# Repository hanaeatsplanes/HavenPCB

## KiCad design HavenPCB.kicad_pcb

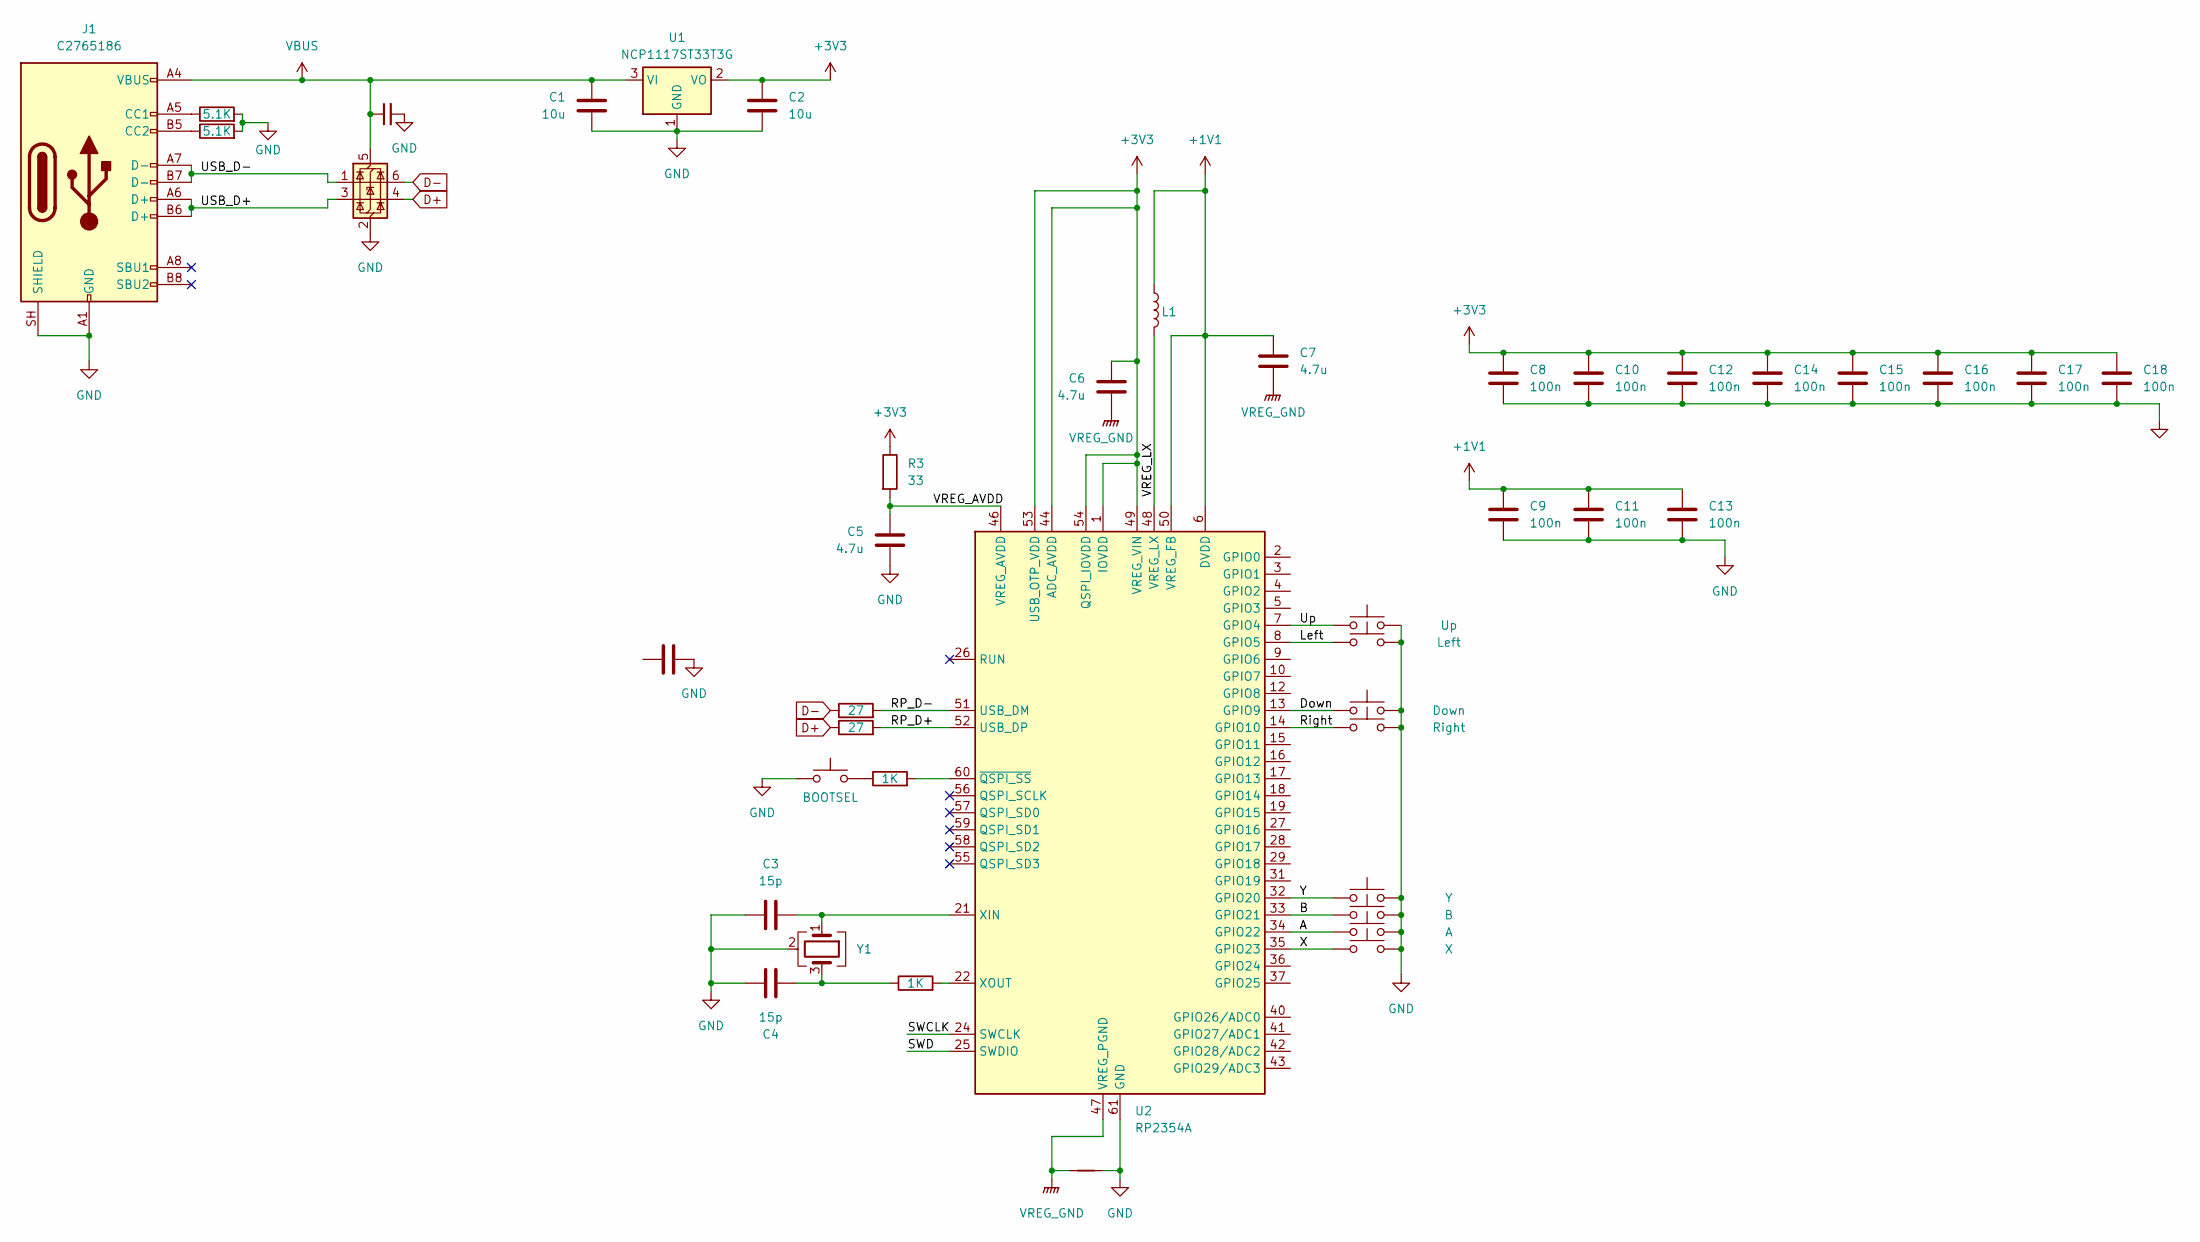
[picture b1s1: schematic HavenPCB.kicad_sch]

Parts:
C1, C2: 10u; C_0402_1005Metric
C3, C4: 15p; C_0402_1005Metric
C5, C6, C7, C22: 4.7u; C_0402_1005Metric
C8, C9, C10, C11, C12, C13, C14, C15, C16, C17, C18, C19: 100n; C_0402_1005Metric
J1: C2765186; USB-C-SMD_TYPE-C-16PIN-2MD-073
L1: AOTA-B201610S3R3-101-T; L_0805_2012Metric
NT1: NetTie_2; NetTie-2_SMD_Pad2.0mm
R1, R2: 5.1K; R_0402_1005Metric
R3: 33; R_0402_1005Metric
R4, R5: 1K; R_0402_1005Metric
R6, R7: 27; R_0603_1608Metric
SW1: BOOTSEL; SW_SPST_TS-1088-xR020
SW2: Up; SW_PUSH_6mm_H5mm
SW3: Right; SW_PUSH_6mm_H5mm
SW4: Left; SW_PUSH_6mm_H5mm
SW5: Down; SW_PUSH_6mm_H5mm
SW6: X; SW_PUSH_6mm_H5mm
SW7: Y; SW_PUSH_6mm_H5mm
SW8: B; SW_PUSH_6mm_H5mm
SW9: A; SW_PUSH_6mm_H5mm
U1: NCP1117ST33T3G; SOT-223-3_TabPin2
U2: RP2354A; QFN-60-1EP_7x7mm_P0.4mm_EP3.4x3.4mm
U3: USBLC6-2SC6; SOT-23-6
Y1: ABM8-272-T3; Crystal_SMD_3225-4Pin_3.2x2.5mm

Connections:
+1V1: C7.1, C9.1, C11.1, C13.1, L1.2, U2.6 (DVDD), U2.23 (DVDD), U2.39 (DVDD), U2.50 (VREG_FB)
+3V3: C2.1, C6.1, C8.1, C10.1, C12.1, C14.1, C15.1, C16.1, C17.1, C18.1, R3.1, U1.2 (VO), U2.1 (IOVDD), U2.11 (IOVDD), U2.20 (IOVDD), U2.30 (IOVDD), U2.38 (IOVDD), U2.44 (ADC_AVDD), U2.45 (IOVDD), U2.49 (VREG_VIN), U2.53 (USB_OTP_VDD), U2.54 (QSPI_IOVDD)
/A: SW9.1, U2.34 (GPIO22)
/B: SW8.1, U2.33 (GPIO21)
/Down: SW5.1, U2.13 (GPIO9)
/Left: SW4.1, U2.8 (GPIO5)
/RP_D+: R7.2, U2.52 (USB_DP)
/RP_D-: R6.2, U2.51 (USB_DM)
/Right: SW3.1, U2.14 (GPIO10)
/SWCLK: U2.24 (SWCLK)
/SWD: U2.25 (SWDIO)
/USB_D+: J1.A6 (D+), J1.B6 (D+), U3.3 (I/O2)
/USB_D-: J1.A7 (D-), J1.B7 (D-), U3.1 (I/O1)
/Up: SW2.1, U2.7 (GPIO4)
/VREG_AVDD: C5.1, R3.2, U2.46 (VREG_AVDD)
/VREG_LX: L1.1, U2.48 (VREG_LX)
/X: SW6.1, U2.35 (GPIO23)
/Y: SW7.1, U2.32 (GPIO20)
D+: R7.1, U3.4 (I/O2)
D-: R6.1, U3.6 (I/O1)
GND: C1.2, C2.2, C3.1, C4.1, C5.2, C8.2, C9.2, C10.2, C11.2, C12.2, C13.2, C14.2, C15.2, C16.2, C17.2, C18.2, C19.2, C22.2, J1.A1 (GND), J1.A12 (GND), J1.B1 (GND), J1.B12 (GND), J1.SH (SHIELD), NT1.2, R1.2, R2.2, SW1.1, SW2.2, SW3.2, SW4.2, SW5.2, SW6.2, SW7.2, SW8.2, SW9.2, U1.1 (GND), U2.61 (GND), U3.2 (GND), Y1.2 (G), Y1.4 (G)
unnamed: C4.2, R5.1, Y1.3
unnamed: J1.A5 (CC1), R1.1
unnamed: J1.B5 (CC2), R2.1
unnamed: R4.1, SW1.2
unnamed: C3.2, U2.21 (XIN), Y1.1
unnamed: R5.2, U2.22 (XOUT)
unnamed: R4.2, U2.60 (~QSPI_SS)
VBUS: C1.1, C19.1, J1.A4 (VBUS), J1.A9 (VBUS), J1.B4 (VBUS), J1.B9 (VBUS), U1.3 (VI), U3.5 (VBUS)
VREG_GND: C6.2, C7.2, NT1.1, U2.47 (VREG_PGND)

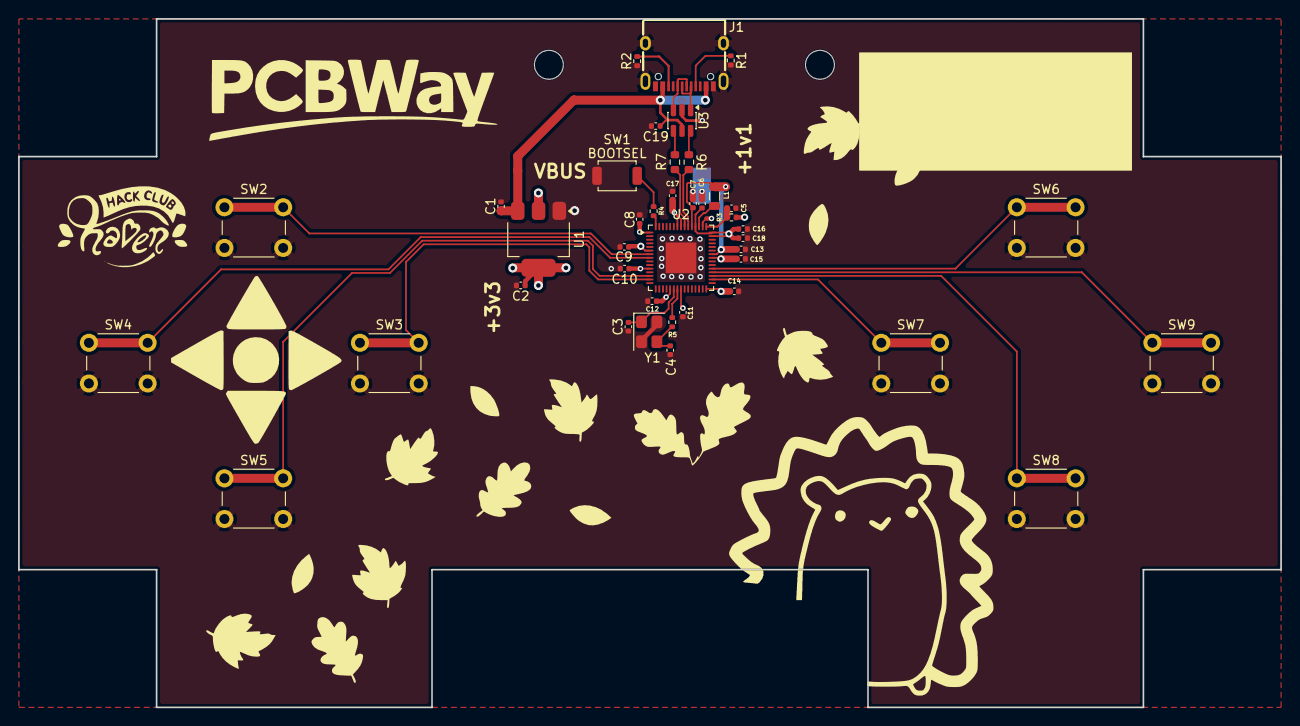
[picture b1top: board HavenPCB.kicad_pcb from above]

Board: 4 copper layers, 139.7 x 76.2 mm, 42 parts (1 on the bottom side), 28 nets.
